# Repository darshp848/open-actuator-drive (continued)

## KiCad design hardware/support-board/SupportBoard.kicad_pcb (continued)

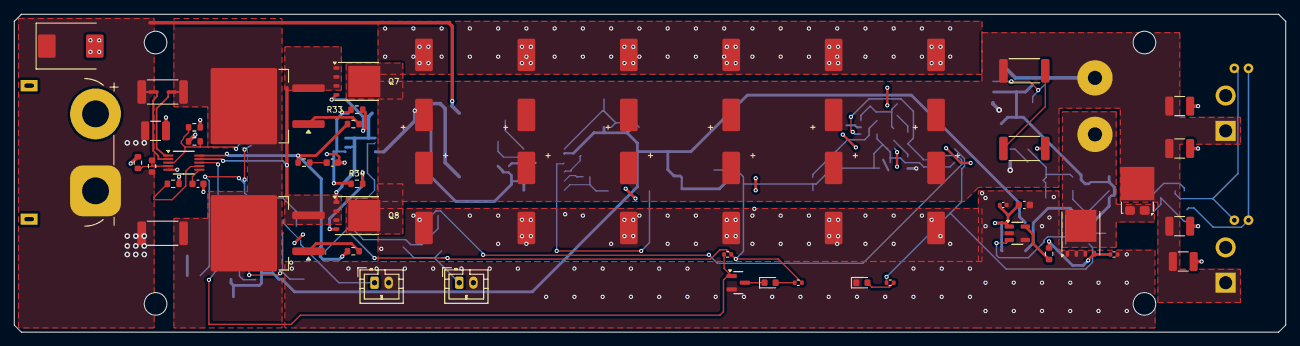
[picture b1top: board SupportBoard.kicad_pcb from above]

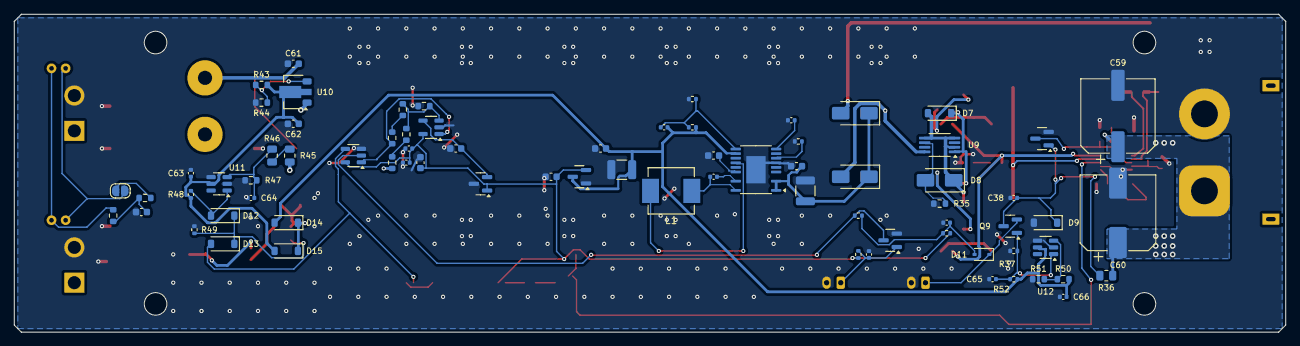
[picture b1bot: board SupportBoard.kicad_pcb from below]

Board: 2 copper layers, 180.0 x 45.0 mm, 139 parts (75 on the bottom side), 61 nets.

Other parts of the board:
H1, H2, H3, H4: MountingHole_3.2mm_M3

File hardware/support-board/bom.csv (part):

ref,value,mpn,footprint,block,note
J1,XT90PW-M battery,XT90PW-M,AMASS_XT90PW-M_1x02_P10.90mm_Horizontal,Input / hot-swap,"Battery input, male PCB XT90 (battery lead carries the female)"
D1,SMCJ58A,SMCJ58A-M3/57T,D_SMC,Input / hot-swap,"Input TVS, VBR 64.4-71.2 V, VC 93.6 V at 16 A (Vishay 88394); C59/C60 take the lead energy first"
C1,1uF 100V,GRM32ER72A105KA01L,C_1210_3225Metric,Input / hot-swap,VIN bypass at U1
C59,33uF 100V,875575961005,CP_Elec_10x12.6,Input / hot-swap,"Input energy absorber, Wurth hybrid polymer, 40 mOhm"
C60,47uF 100V,EEE-FN2A470UP,CP_Elec_10x10.5,Input / hot-swap,"Input damping, 0.7 ohm ESR damps the lead / ceramic LC ring"
RS1,1.8m 1% 3W,CSS2H-2512K-1L80FE,R_2512_6332Metric,Input / hot-swap,"Sense, 2 x 1.8 mOhm = 0.9 mOhm: I_LIM 53.4-69.0 A"
RS2,1.8m 1% 3W,CSS2H-2512K-1L80FE,R_2512_6332Metric,Input / hot-swap,
U1,LM5069MM-2/NOPB,LM5069MM-2/NOPB,VSSOP-10_3x3mm_P0.5mm,Input / hot-swap,
Q1,CSD19536KTT,CSD19536KTTT,TO-263-2,Input / hot-swap,
R3,10R,RC0603FR-0710RL,R_0603_1608Metric,Input / hot-swap,Per-FET gate resistor (parallel FETs)
Q2,CSD19536KTT,CSD19536KTTT,TO-263-2,Input / hot-swap,
R4,10R,RC0603FR-0710RL,R_0603_1608Metric,Input / hot-swap,Per-FET gate resistor (parallel FETs)
R5,71.5k 1%,RC0603FR-0771K5L,R_0603_1608Metric,Input / hot-swap,"UVLO: on 19.2 V, off 17.7 V (21 uA hysteresis)"
R6,10.7k 1%,RC0603FR-0710K7L,R_0603_1608Metric,Input / hot-swap,
R7,71.5k 1%,RC0603FR-0771K5L,R_0603_1608Metric,Input / hot-swap,"OVLO: off 59.1 V, on 57.6 V (above the 57.1 V chopper)"
R8,3.16k 1%,RC0603FR-073K16L,R_0603_1608Metric,Input / hot-swap,
R9,27.4k 1%,RC0603FR-0727K4L,R_0603_1608Metric,Input / hot-swap,Power limit 305 W at 54 V with 0.9 mOhm (VSNS 5.1 mV >= 5 mV floor)
C2,15nF,C0603C153K5RACTU,C_0603_1608Metric,Input / hot-swap,Fault timer 0.71 ms (0.42-1.35 ms); insertion delay 11 ms
R10,1k,RC0603FR-071KL,R_0603_1608Metric,Input / hot-swap,"dv/dt start: 16 uA / 47 nF = 340 V/s, ~1 A into 3 mF"
C3,47nF 100V,C0603C473K1RACTU,C_0603_1608Metric,Input / hot-swap,Gate-to-ground dv/dt capacitor sees about BUS + 12 V; DC-bias startup qualification remains open
Q4,BSS138,BSS138,SOT-23,Input / hot-swap,RUN_INH high (default) -> UVLO held low -> hot-swap off
R11,100k,RC0402FR-07100KL,R_0402_1005Metric,Input / hot-swap,
Q5,BSS138,BSS138,SOT-23,Input / hot-swap,
D5,green PGD,150060GS75000,LED_0603_1608Metric,Input / hot-swap,PGD released indication only; does not prove bus voltage or input validity
R12,1k,RC0402FR-071KL,R_0402_1005Metric,Input / hot-swap,
Q7,BSC040N10NS5ATMA1,BSC040N10NS5ATMA1,TDSON-8-1,Input / hot-swap,"Ideal-diode FET: source HS_S, drain BUS+ (2 x 4 mOhm in parallel)"
R33,10R,RC0603FR-0710RL,R_0603_1608Metric,Input / hot-swap,Per-FET gate resistor (parallel FETs)
Q8,BSC040N10NS5ATMA1,BSC040N10NS5ATMA1,TDSON-8-1,Input / hot-swap,"Ideal-diode FET: source HS_S, drain BUS+ (2 x 4 mOhm in parallel)"
R34,10R,RC0603FR-0710RL,R_0603_1608Metric,Input / hot-swap,Per-FET gate resistor (parallel FETs)
U9,LTC4359IMS8#PBF,LTC4359IMS8#PBF,MSOP-8_3x3mm_P0.65mm,Input / hot-swap,Ideal diode controller: blocks regeneration into the source
D7,BZT52C12,BZT52C12-7-F,D_SOD-123,Input / hot-swap,"12 V gate-source clamp (LTC4359 D4, required at 24 V and above)"
D8,SMAT70A,SMAT70A,D_SMA,Input / hot-swap,IN/SOURCE positive clamp to VSS (LTC4359 D1)
R35,1k,RC0603FR-071KL,R_0603_1608Metric,Input / hot-swap,VSS resistor (LTC4359 R1): keeps fast turn-off with the TVS
C20,130uF 80V,B40910A0137M000,TDK_B40910_10x16p5_DRAFT,Bank / chain outputs,
C21,130uF 80V,B40910A0137M000,TDK_B40910_10x16p5_DRAFT,Bank / chain outputs,
C22,130uF 80V,B40910A0137M000,TDK_B40910_10x16p5_DRAFT,Bank / chain outputs,
C23,130uF 80V,B40910A0137M000,TDK_B40910_10x16p5_DRAFT,Bank / chain outputs,
C24,130uF 80V,B40910A0137M000,TDK_B40910_10x16p5_DRAFT,Bank / chain outputs,
C25,130uF 80V,B40910A0137M000,TDK_B40910_10x16p5_DRAFT,Bank / chain outputs,
C26,130uF 80V,B40910A0137M000,TDK_B40910_10x16p5_DRAFT,Bank / chain outputs,
C27,130uF 80V,B40910A0137M000,TDK_B40910_10x16p5_DRAFT,Bank / chain outputs,
C28,130uF 80V,B40910A0137M000,TDK_B40910_10x16p5_DRAFT,Bank / chain outputs,
C29,130uF 80V,B40910A0137M000,TDK_B40910_10x16p5_DRAFT,Bank / chain outputs,
C30,130uF 80V,B40910A0137M000,TDK_B40910_10x16p5_DRAFT,Bank / chain outputs,
C31,130uF 80V,B40910A0137M000,TDK_B40910_10x16p5_DRAFT,Bank / chain outputs,
C32,1uF 100V,GRM32ER72A105KA01L,C_1210_3225Metric,Bank / chain outputs,HF bypass at the chain outputs
C33,1uF 100V,GRM32ER72A105KA01L,C_1210_3225Metric,Bank / chain outputs,HF bypass at the chain outputs
C34,1uF 100V,GRM32ER72A105KA01L,C_1210_3225Metric,Bank / chain outputs,HF bypass at the chain outputs
C35,1uF 100V,GRM32ER72A105KA01L,C_1210_3225Metric,Bank / chain outputs,HF bypass at the chain outputs
R13,10k 0.5W,RC2512FK-0710KL,R_2512_6332Metric,Bank / chain outputs,Bleeder: 3 mF from 54 V to 5 V in ~150 s
R14,10k 0.5W,RC2512FK-0710KL,R_2512_6332Metric,Bank / chain outputs,
J2,XT30PW(2+2)-M chain,XT30PW(2+2)-M.G.B,XT30PW22M,Bank / chain outputs,Same pinout as the actuator J1/J5
J3,XT30PW(2+2)-M chain,XT30PW(2+2)-M.G.B,XT30PW22M,Bank / chain outputs,Same pinout as the actuator J1/J5
JP1,CAN TERM,,SolderJumper-2_P1.3mm_Open_RoundedPad1.0x1.5mm,Bank / chain outputs,Close to terminate the chain at the support board
R15,60.4R,RC0603FR-0760R4L,R_0603_1608Metric,Bank / chain outputs,
R16,60.4R,RC0603FR-0760R4L,R_0603_1608Metric,Bank / chain outputs,
C36,4.7nF,GRM188R71H472KA01D,C_0603_1608Metric,Bank / chain outputs,
R20,150k 0.1%,TNPW0603150KBETA,R_0603_1608Metric,Brake chopper,Threshold 57.1 V on / 55.0 V off
R21,150k 0.1%,TNPW0603150KBETA,R_0603_1608Metric,Brake chopper,
R22,6.81k 0.1%,TNPW06036K81BETA,R_0603_1608Metric,Brake chopper,
R23,237k 0.1%,TNPW0603237KBETA,R_0603_1608Metric,Brake chopper,
R24,237k 0.1%,TNPW0603237KBETA,R_0603_1608Metric,Brake chopper,
U3,TLV3201AIDBVR,TLV3201AIDBVR,SOT-23-5,Brake chopper,
U4,REF3312AIDBZR,REF3312AIDBZR,SOT-23,Brake chopper,
C40,0.1uF,GCM155R71E104KE02D,C_0402_1005Metric,Brake chopper,
C41,1uF,C1608X7R1E105K080AE,C_0603_1608Metric,Brake chopper,
C42,1uF,C1608X7R1E105K080AE,C_0603_1608Metric,Brake chopper,
U5,SN74LVC1G32DBVR,SN74LVC1G32DBVR,SOT-23-5,Brake chopper,Chopper on = overvoltage OR discharge request
C43,0.1uF,GCM155R71E104KE02D,C_0402_1005Metric,Brake chopper,
U6,UCC27517DBVR,UCC27517DBVT,SOT-23-5,Brake chopper,IN+ = primary CH_CMD OR backup CHB_OV; VDD = +12V OR V_CHB (aux-loss fix 2026-10-25)
C44,0.1uF 25V,GCM155R71E104KE02D,C_0402_1005Metric,Brake chopper,
C45,1uF 25V,C1608X7R1E105K080AE,C_0603_1608Metric,Brake chopper,
D13,1N5819HW,1N5819HW-7-F,D_SOD-123,Brake chopper,Primary command into the driver OR (3.2 V - 0.3 V > VIN_H 2.4 V)
R49,100k,RC0402FR-07100KL,R_0402_1005Metric,Brake chopper,Driver input pull-down
D14,1N5819HW,1N5819HW-7-F,D_SOD-123,Brake chopper,Driver supply from the aux 12 V
R25,4.7R,RC0603FR-074R7L,R_0603_1608Metric,Brake chopper,
R26,10k,RC0402FR-0710KL,R_0402_1005Metric,Brake chopper,
Q3,BSC040N10NS5ATMA1,BSC040N10NS5ATMA1,TDSON-8-1,Brake chopper,Chopper switch: 21.6 A into 2.5 ohm at 54 V
D2,V10P10-M3/86A,V10P10-M3/86A,TO-277A,Brake chopper,Freewheel across the resistor harness
J4,BRAKE RESISTOR,,PowerWire_P8,Brake chopper,"Wire pads to BrakeResistor J1 (1 = BRK+, 2 = switched end)"
D6,red BRAKE,150060RS75000,LED_0603_1608Metric,Brake chopper,
R27,1k,RC0402FR-071KL,R_0402_1005Metric,Brake chopper,
U10,LR8N8-G,LR8N8-G,SOT-89-3,Backup OV brake,Bus-powered 10 V for the backup channel (9.5-10.7 V); needs BUS+ >= 22.7 V
C61,0.1uF 100V,GCJ188R72A104KA01D,C_0603_1608Metric,Backup OV brake,
R43,2.4k 1%,RC0603FR-072K4L,R_0603_1608Metric,Backup OV brake,LR8 R1: also its 0.5 mA minimum load
R44,17.4k 1%,RC0603FR-0717K4L,R_0603_1608Metric,Backup OV brake,LR8 R2: 1.20 V x 8.25 + 10 uA x 17.4k = 10.07 V
C62,1uF 25V,C1608X7R1E105K080AE,C_0603_1608Metric,Backup OV brake,LR8 output (>= 1 uF)
D15,1N5819HW,1N5819HW-7-F,D_SOD-123,Backup OV brake,Driver supply from the bus when the aux is gone
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
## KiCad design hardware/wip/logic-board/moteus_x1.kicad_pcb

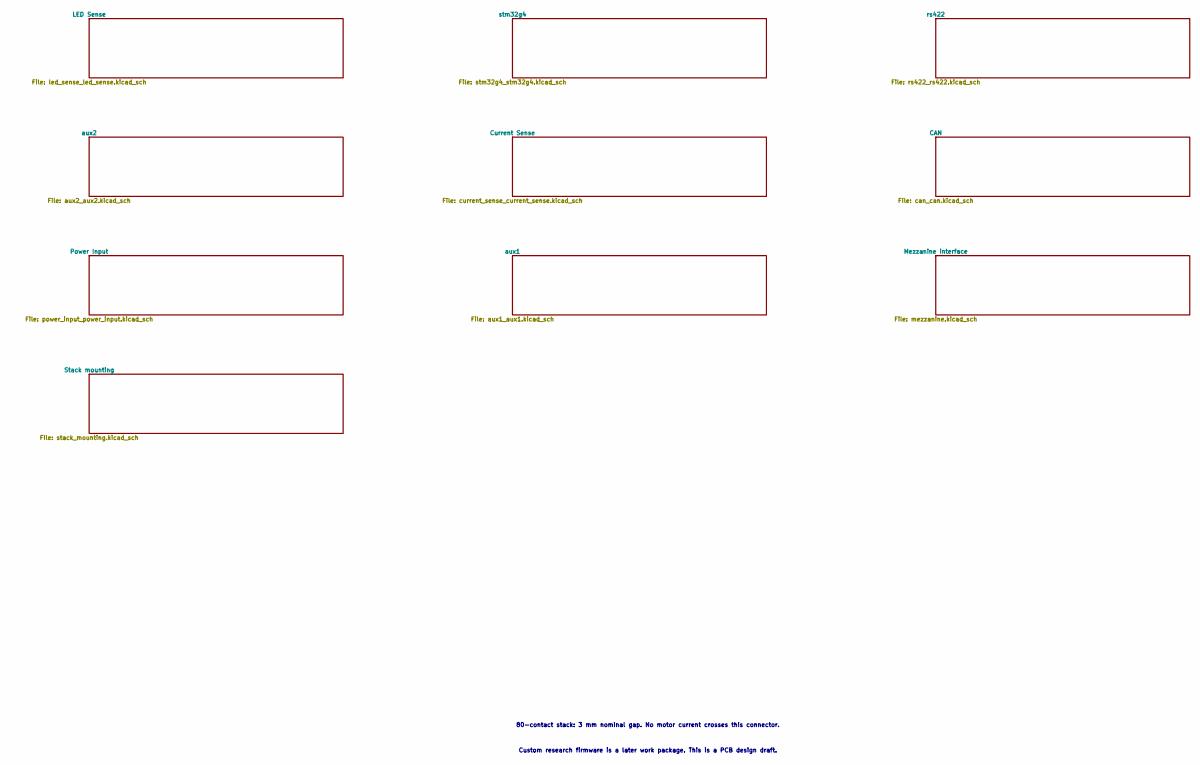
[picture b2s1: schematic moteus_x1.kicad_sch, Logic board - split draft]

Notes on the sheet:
Custom research firmware is a later work package. This is a PCB design draft.
80-contact stack: 3 mm nominal gap. No motor current crosses this connector.

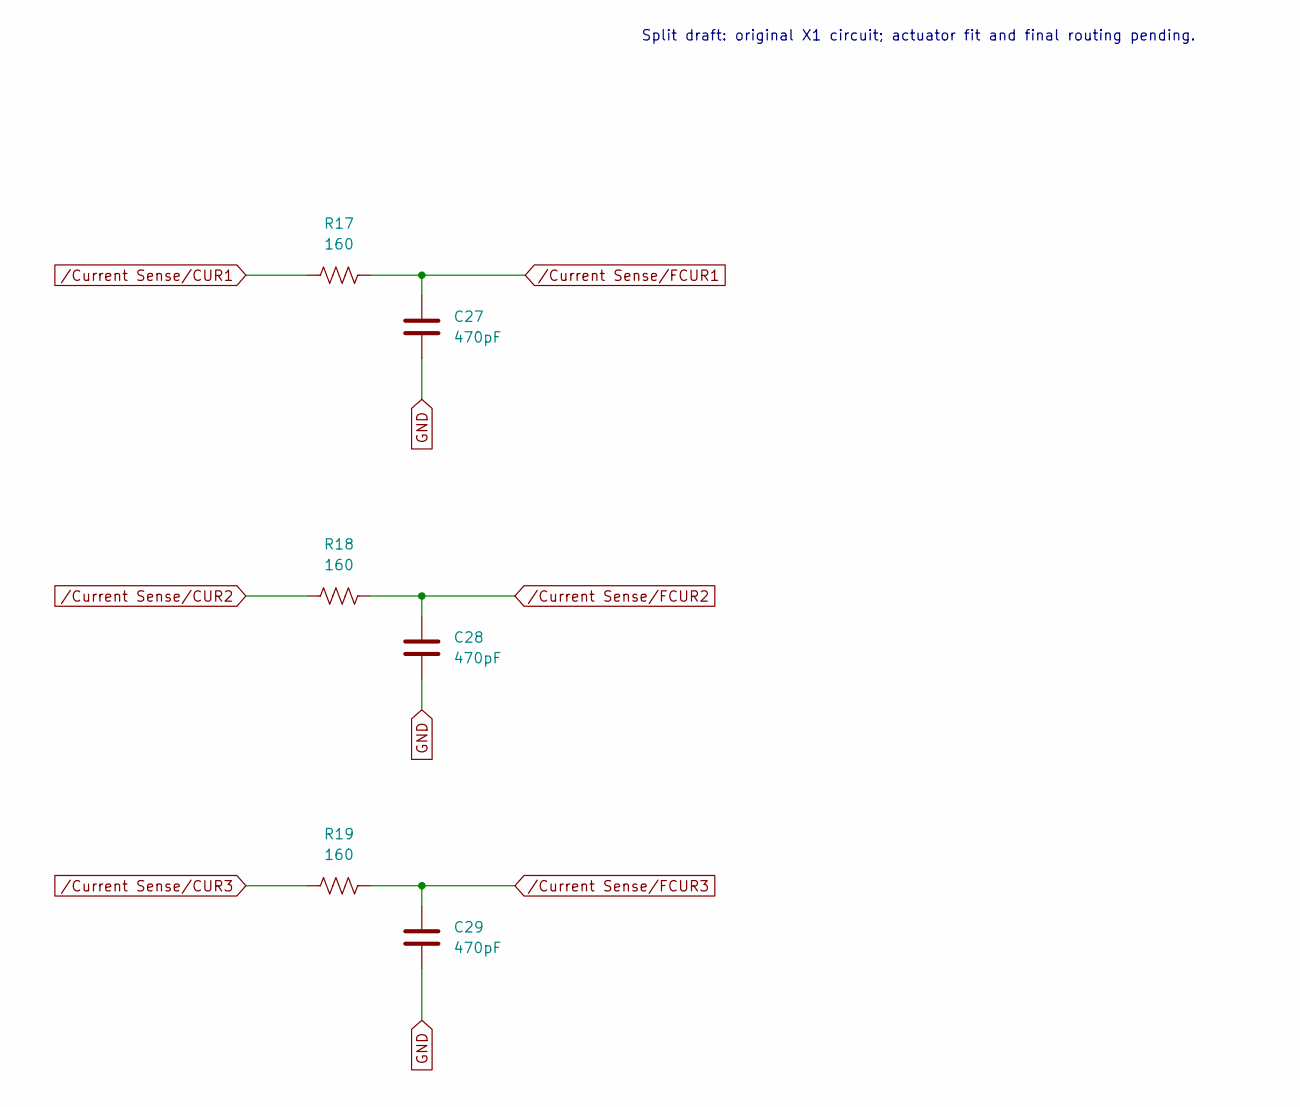
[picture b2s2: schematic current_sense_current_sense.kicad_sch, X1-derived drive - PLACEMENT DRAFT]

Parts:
C27, C28, C29: 470pF; C_0402_1005Metric; MPN GCM1555C1H471JA16D
R17, R18, R19: 160; R_0402_1005Metric; MPN RC0402FR-07160RL

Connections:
GND: C27.2, C28.2, C29.2; also elsewhere on the board
/Current Sense/CUR1: R17.1; also elsewhere on the board
/Current Sense/CUR2: R18.1; also elsewhere on the board
/Current Sense/CUR3: R19.1; also elsewhere on the board
/Current Sense/FCUR1: C27.1, R17.2; also elsewhere on the board
/Current Sense/FCUR2: C28.1, R18.2; also elsewhere on the board
/Current Sense/FCUR3: C29.1, R19.2; also elsewhere on the board

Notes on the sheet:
Split draft: original X1 circuit; actuator fit and final routing pending.

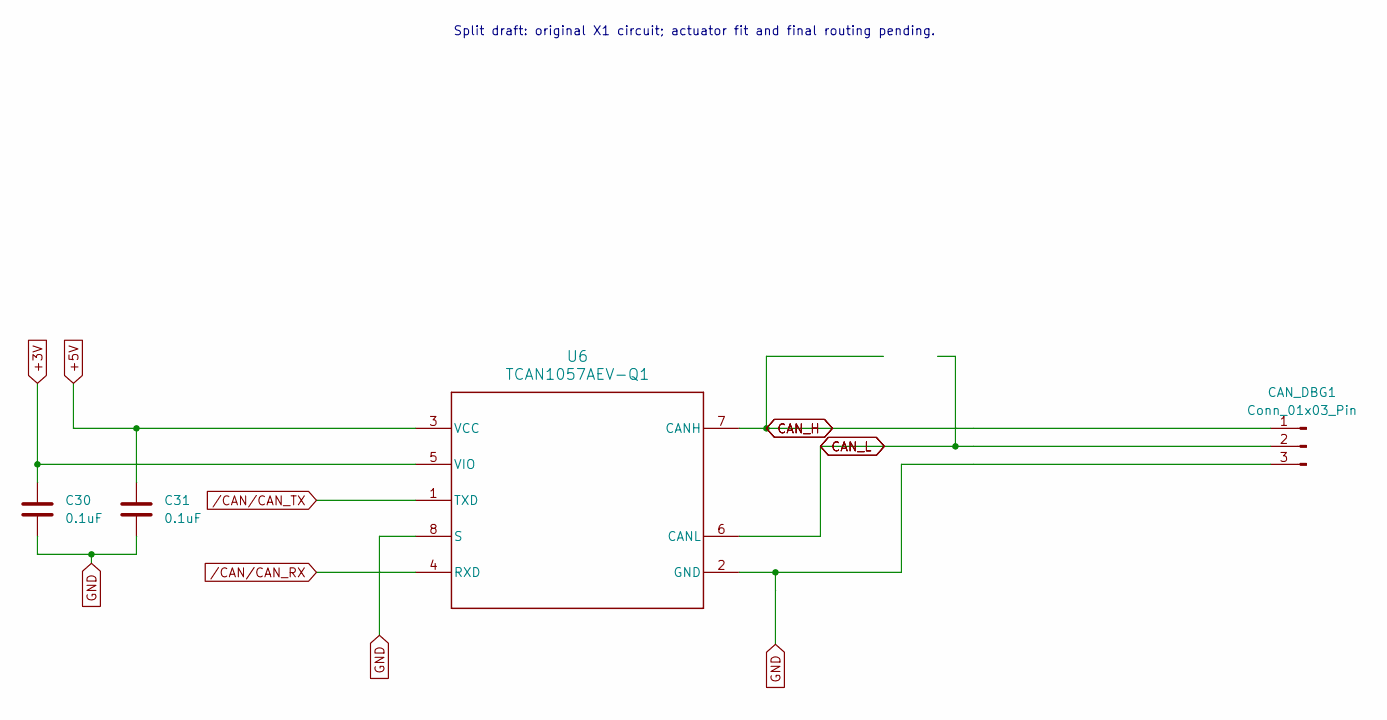
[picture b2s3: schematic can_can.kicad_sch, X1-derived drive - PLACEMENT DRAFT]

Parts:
C30, C31: 0.1uF; C_0402_1005Metric; MPN MF-CAP-0402-0.1uF
CAN_DBG1: Conn_01x03_Pin; PinHeader_1x03_P2.00mm_Vertical
U6: TCAN1057AEV-Q1; SOIC-8_3.9x4.9mm_P1.27mm; MPN TCAN1057AEVDRQ1

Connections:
+3V: C30.1, U6.5 (VIO); also elsewhere on the board
+5V: C31.1, U6.3 (VCC); also elsewhere on the board
CAN_H: CAN_DBG1.1, U6.7 (CANH); also elsewhere on the board
CAN_L: CAN_DBG1.2, U6.6 (CANL); also elsewhere on the board
GND: C30.2, C31.2, CAN_DBG1.3, U6.2 (GND), U6.8 (S); also elsewhere on the board
/CAN/CAN_RX: U6.4 (RXD); also elsewhere on the board
/CAN/CAN_TX: U6.1 (TXD); also elsewhere on the board

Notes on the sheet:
Split draft: original X1 circuit; actuator fit and final routing pending.

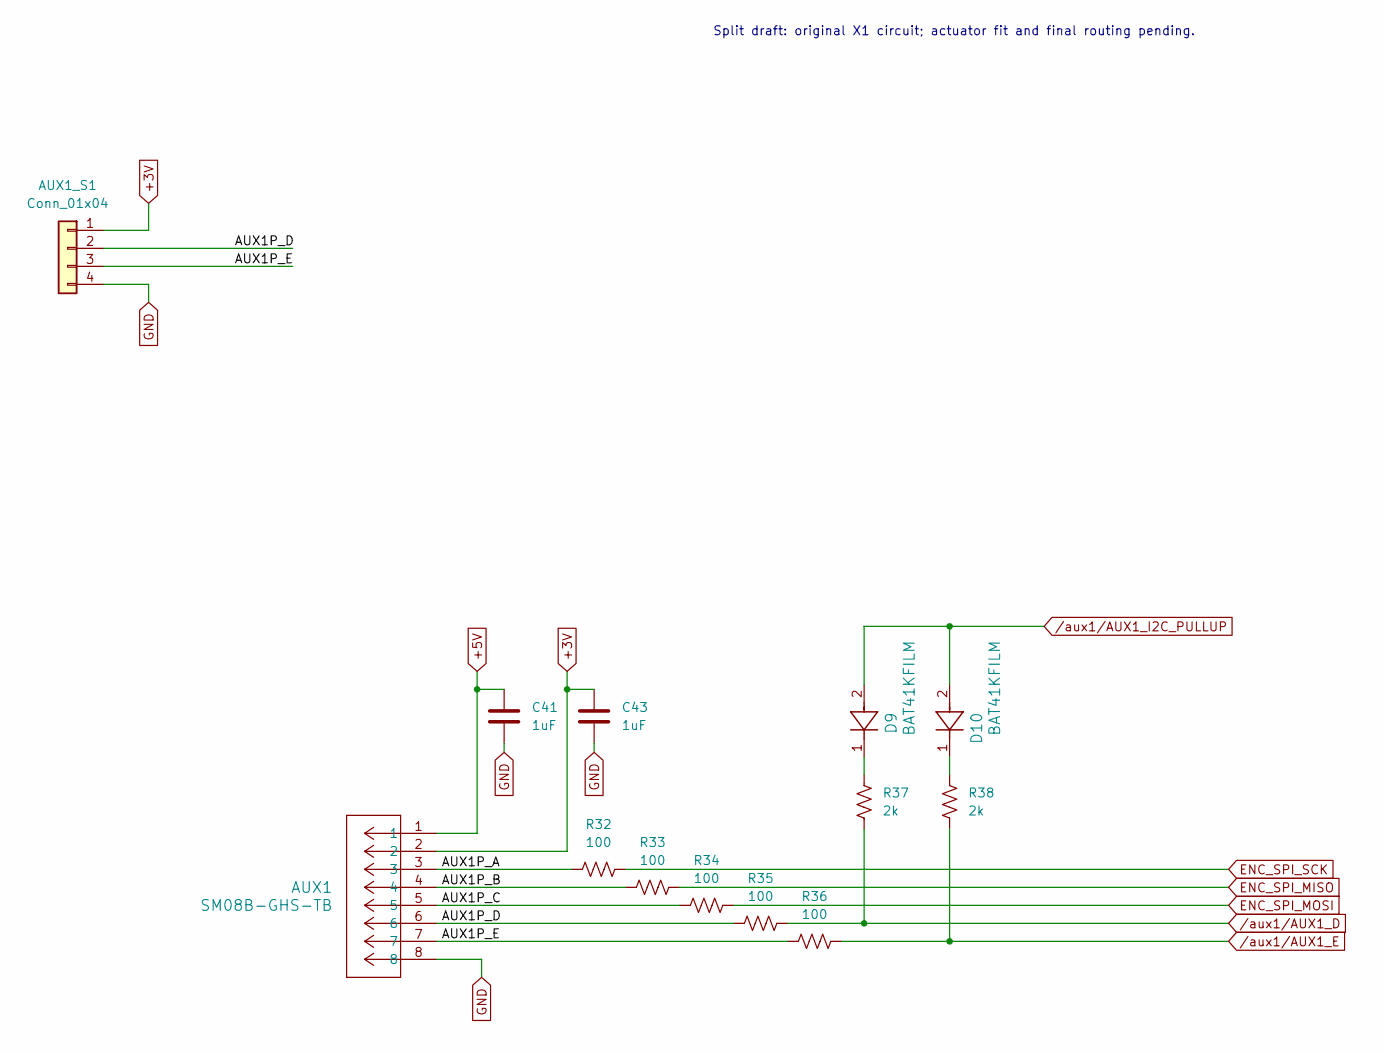
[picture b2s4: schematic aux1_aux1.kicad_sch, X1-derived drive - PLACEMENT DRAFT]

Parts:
AUX1: SM08B-GHS-TB; CONN_SM08B-GHS-TB_JST; MPN SM08B-GHS-TB(LF)(SN)
AUX1_S1: Conn_01x04; PinHeader_1x04_P1.27mm_Vertical
C41, C43: 1uF; C_0402_1005Metric; MPN MF-CAP-0402-1uF
D9, D10: BAT41KFILM; SOD-523_STM; MPN BAT41KFILM
R32, R33, R34, R35, R36: 100; R_0402_1005Metric; MPN MF-RES-0402-100
R37, R38: 2k; R_0402_1005Metric; MPN MF-RES-0402-2K

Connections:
+3V: AUX1.2, AUX1_S1.1, C43.1; also elsewhere on the board
+5V: AUX1.1, C41.1; also elsewhere on the board
/aux1/AUX1P_A: AUX1.3, R32.1
/aux1/AUX1P_B: AUX1.4, R33.1
/aux1/AUX1P_C: AUX1.5, R34.1
/aux1/AUX1P_D: AUX1.6, AUX1_S1.2, R35.1
/aux1/AUX1P_E: AUX1.7, AUX1_S1.3, R36.1
ENC_SPI_MISO: R33.2; also elsewhere on the board
ENC_SPI_MOSI: R34.2; also elsewhere on the board
ENC_SPI_SCK: R32.2; also elsewhere on the board
GND: AUX1.8, AUX1_S1.4, C41.2, C43.2; also elsewhere on the board
unnamed: D9.1, R37.1
unnamed: D10.1, R38.1
/aux1/AUX1_D: R35.2, R37.2; also elsewhere on the board
/aux1/AUX1_E: R36.2, R38.2; also elsewhere on the board
/aux1/AUX1_I2C_PULLUP: D9.2, D10.2; also elsewhere on the board

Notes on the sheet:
Split draft: original X1 circuit; actuator fit and final routing pending.

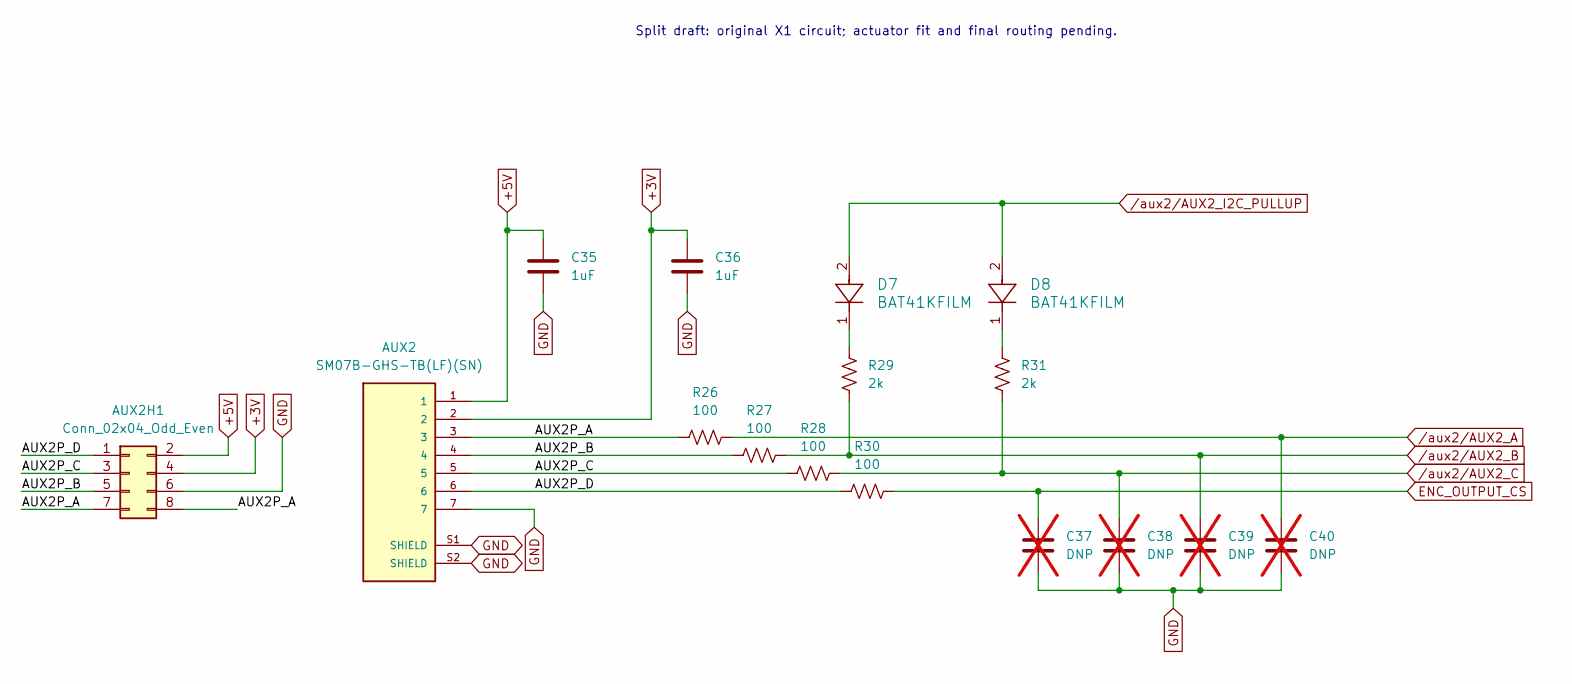
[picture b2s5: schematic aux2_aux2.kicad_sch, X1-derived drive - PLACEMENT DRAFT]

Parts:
AUX2: SM07B-GHS-TB(LF)(SN); JST_SM07B-GHS-TB(LF)(SN); MPN SM07B-GHS-TB(LF)(SN)
AUX2H1: Conn_02x04_Odd_Even; PinHeader_2x04_P1.27mm_Vertical
C35, C36: 1uF; C_0402_1005Metric; MPN MF-CAP-0402-1uF
C37, C38, C39, C40: DNP; C_0402_1005Metric; not fitted
D7, D8: BAT41KFILM; SOD-523_STM; MPN BAT41KFILM
R26, R27, R28, R30: 100; R_0402_1005Metric; MPN MF-RES-0402-100
R29, R31: 2k; R_0402_1005Metric; MPN MF-RES-0402-2K

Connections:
+3V: AUX2.2, AUX2H1.4, C36.1; also elsewhere on the board
+5V: AUX2.1, AUX2H1.2, C35.1; also elsewhere on the board
/aux2/AUX2P_A: AUX2.3, AUX2H1.7, AUX2H1.8, R26.1
/aux2/AUX2P_B: AUX2.4, AUX2H1.5, R27.1
/aux2/AUX2P_C: AUX2.5, AUX2H1.3, R28.1
/aux2/AUX2P_D: AUX2.6, AUX2H1.1, R30.1
ENC_OUTPUT_CS: C37.1, R30.2; also elsewhere on the board
GND: AUX2.7, AUX2.S1 (SHIELD), AUX2.S2 (SHIELD), AUX2H1.6, C35.2, C36.2, C37.2, C38.2, C39.2, C40.2; also elsewhere on the board
unnamed: D7.1, R29.1
unnamed: D8.1, R31.1
/aux2/AUX2_A: C40.1, R26.2; also elsewhere on the board
/aux2/AUX2_B: C39.1, R27.2, R29.2; also elsewhere on the board
/aux2/AUX2_C: C38.1, R28.2, R31.2; also elsewhere on the board
/aux2/AUX2_I2C_PULLUP: D7.2, D8.2; also elsewhere on the board

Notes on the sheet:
Split draft: original X1 circuit; actuator fit and final routing pending.

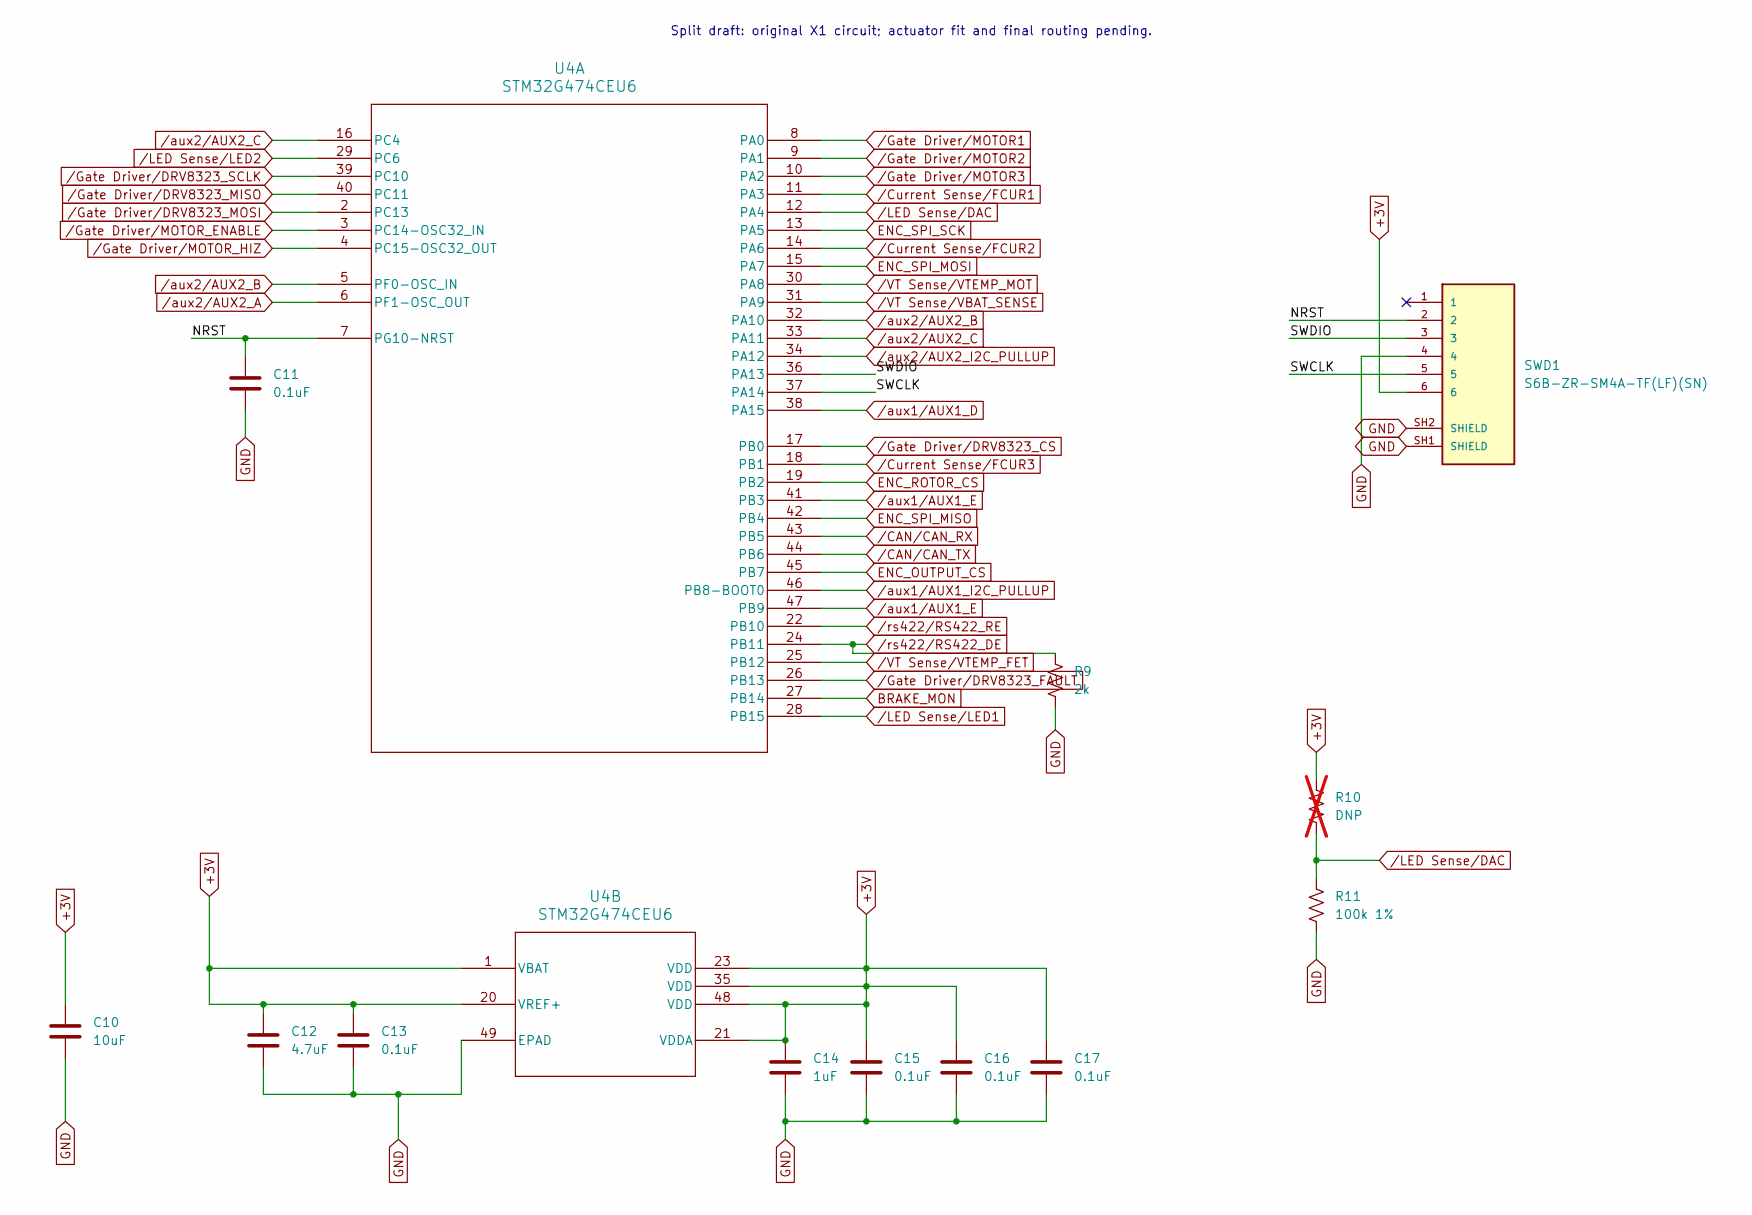
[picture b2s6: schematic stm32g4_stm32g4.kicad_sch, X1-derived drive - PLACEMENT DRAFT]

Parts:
C10: 10uF; C_1206_3216Metric; MPN MF-CAP-1206-10uF
C11, C13, C15, C16, C17: 0.1uF; C_0402_1005Metric; MPN MF-CAP-0402-0.1uF
C12: 4.7uF; C_0603_1608Metric; MPN CL10A475KP8NNNC
C14: 1uF; C_0402_1005Metric; MPN MF-CAP-0402-1uF
R9: 2k; R_0402_1005Metric; MPN MF-RES-0402-2K
R10: DNP; R_0402_1005Metric; not fitted
R11: 100k 1%; R_0402_1005Metric; MPN RC0402FR-07100KL
SWD1: S6B-ZR-SM4A-TF(LF)(SN); JST_S6B-ZR-SM4A-TF(LF)(SN); MPN S6B-ZR-SM4A-TF(LF)(SN)
U4: STM32G474CEU6; UFQFPN-48_7X7X0P55MM; MPN STM32G474CEU6

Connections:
+3V: C10.1, C12.1, C13.1, C14.1, C15.1, C16.1, C17.1, R10.1, SWD1.6, U4.1 (VBAT), U4.20 (VREF+), U4.21 (VDDA), U4.23 (VDD), U4.35 (VDD), U4.48 (VDD); also elsewhere on the board
/stm32g4/NRST: C11.1, SWD1.2, U4.7 (PG10-NRST)
/stm32g4/SWCLK: SWD1.5, U4.37 (PA14)
/stm32g4/SWDIO: SWD1.3, U4.36 (PA13)
BRAKE_MON: U4.27 (PB14); also elsewhere on the board
ENC_OUTPUT_CS: U4.45 (PB7); also elsewhere on the board
ENC_ROTOR_CS: U4.19 (PB2); also elsewhere on the board
ENC_SPI_MISO: U4.42 (PB4); also elsewhere on the board
ENC_SPI_MOSI: U4.15 (PA7); also elsewhere on the board
ENC_SPI_SCK: U4.13 (PA5); also elsewhere on the board
GND: C10.2, C11.2, C12.2, C13.2, C14.2, C15.2, C16.2, C17.2, R9.2, R11.2, SWD1.4, SWD1.SH1 (SHIELD), SWD1.SH2 (SHIELD), U4.49 (EPAD); also elsewhere on the board
/CAN/CAN_RX: U4.43 (PB5); also elsewhere on the board
/CAN/CAN_TX: U4.44 (PB6); also elsewhere on the board
/Current Sense/FCUR1: U4.11 (PA3); also elsewhere on the board
/Current Sense/FCUR2: U4.14 (PA6); also elsewhere on the board
/Current Sense/FCUR3: U4.18 (PB1); also elsewhere on the board
/Gate Driver/DRV8323_CS: U4.17 (PB0); also elsewhere on the board
/Gate Driver/DRV8323_FAULT: U4.26 (PB13); also elsewhere on the board
/Gate Driver/DRV8323_MISO: U4.40 (PC11); also elsewhere on the board
/Gate Driver/DRV8323_MOSI: U4.2 (PC13); also elsewhere on the board
/Gate Driver/DRV8323_SCLK: U4.39 (PC10); also elsewhere on the board
/Gate Driver/MOTOR1: U4.8 (PA0); also elsewhere on the board
/Gate Driver/MOTOR2: U4.9 (PA1); also elsewhere on the board
/Gate Driver/MOTOR3: U4.10 (PA2); also elsewhere on the board
/Gate Driver/MOTOR_ENABLE: U4.3 (PC14-OSC32_IN); also elsewhere on the board
/Gate Driver/MOTOR_HIZ: U4.4 (PC15-OSC32_OUT); also elsewhere on the board
/LED Sense/DAC: R10.2, R11.1, U4.12 (PA4); also elsewhere on the board
/LED Sense/LED1: U4.28 (PB15); also elsewhere on the board
/LED Sense/LED2: U4.29 (PC6); also elsewhere on the board
/VT Sense/VBAT_SENSE: U4.31 (PA9); also elsewhere on the board
/VT Sense/VTEMP_FET: U4.25 (PB12); also elsewhere on the board
/VT Sense/VTEMP_MOT: U4.30 (PA8); also elsewhere on the board
/aux1/AUX1_D: U4.38 (PA15); also elsewhere on the board
/aux1/AUX1_E: U4.41 (PB3), U4.47 (PB9); also elsewhere on the board
/aux1/AUX1_I2C_PULLUP: U4.46 (PB8-BOOT0); also elsewhere on the board
/aux2/AUX2_A: U4.6 (PF1-OSC_OUT); also elsewhere on the board
/aux2/AUX2_B: U4.5 (PF0-OSC_IN), U4.32 (PA10); also elsewhere on the board
/aux2/AUX2_C: U4.16 (PC4), U4.33 (PA11); also elsewhere on the board
/aux2/AUX2_I2C_PULLUP: U4.34 (PA12); also elsewhere on the board
/rs422/RS422_DE: R9.1, U4.24 (PB11); also elsewhere on the board
/rs422/RS422_RE: U4.22 (PB10); also elsewhere on the board

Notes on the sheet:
Split draft: original X1 circuit; actuator fit and final routing pending.

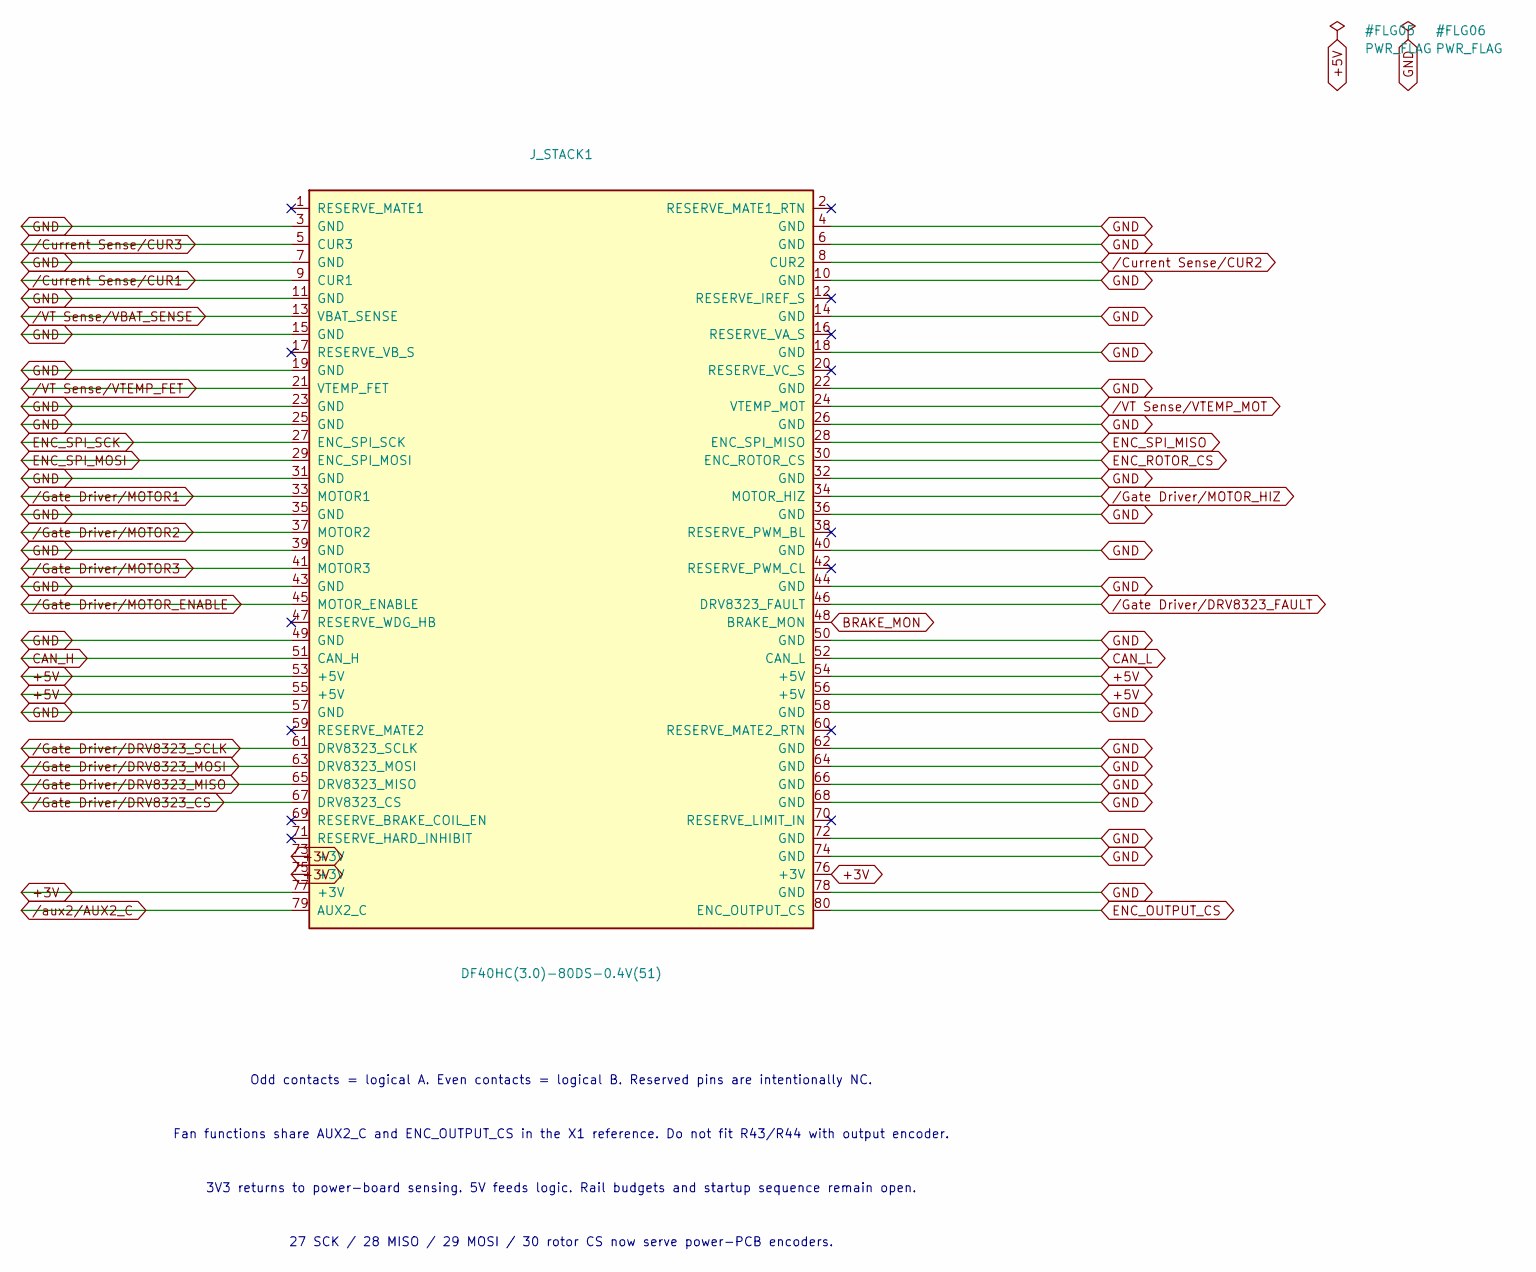
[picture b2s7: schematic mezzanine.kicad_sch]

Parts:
J_STACK1: DF40HC(3.0)-80DS-0.4V(51); Hirose_DF40HC(3.0)-80DS-0.4V_2x40_P0.4mm; MPN DF40HC(3.0)-80DS-0.4V(51)

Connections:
+3V: J_STACK1.73 (+3V), J_STACK1.75 (+3V), J_STACK1.76 (+3V), J_STACK1.77 (+3V); also elsewhere on the board
+5V: J_STACK1.53 (+5V), J_STACK1.54 (+5V), J_STACK1.55 (+5V), J_STACK1.56 (+5V); also elsewhere on the board
BRAKE_MON: J_STACK1.48 (BRAKE_MON); also elsewhere on the board
CAN_H: J_STACK1.51 (CAN_H); also elsewhere on the board
CAN_L: J_STACK1.52 (CAN_L); also elsewhere on the board
ENC_OUTPUT_CS: J_STACK1.80 (ENC_OUTPUT_CS); also elsewhere on the board
ENC_ROTOR_CS: J_STACK1.30 (ENC_ROTOR_CS); also elsewhere on the board
ENC_SPI_MISO: J_STACK1.28 (ENC_SPI_MISO); also elsewhere on the board
ENC_SPI_MOSI: J_STACK1.29 (ENC_SPI_MOSI); also elsewhere on the board
ENC_SPI_SCK: J_STACK1.27 (ENC_SPI_SCK); also elsewhere on the board
GND: J_STACK1.3 (GND), J_STACK1.4 (GND), J_STACK1.6 (GND), J_STACK1.7 (GND), J_STACK1.10 (GND), J_STACK1.11 (GND), J_STACK1.14 (GND), J_STACK1.15 (GND), J_STACK1.18 (GND), J_STACK1.19 (GND), J_STACK1.22 (GND), J_STACK1.23 (GND), J_STACK1.25 (GND), J_STACK1.26 (GND), J_STACK1.31 (GND), J_STACK1.32 (GND), J_STACK1.35 (GND), J_STACK1.36 (GND), J_STACK1.39 (GND), J_STACK1.40 (GND), J_STACK1.43 (GND), J_STACK1.44 (GND), J_STACK1.49 (GND), J_STACK1.50 (GND), J_STACK1.57 (GND), J_STACK1.58 (GND), J_STACK1.62 (GND), J_STACK1.64 (GND), J_STACK1.66 (GND), J_STACK1.68 (GND), J_STACK1.72 (GND), J_STACK1.74 (GND), J_STACK1.78 (GND); also elsewhere on the board
/Current Sense/CUR1: J_STACK1.9 (CUR1); also elsewhere on the board
/Current Sense/CUR2: J_STACK1.8 (CUR2); also elsewhere on the board
/Current Sense/CUR3: J_STACK1.5 (CUR3); also elsewhere on the board
/Gate Driver/DRV8323_CS: J_STACK1.67 (DRV8323_CS); also elsewhere on the board
/Gate Driver/DRV8323_FAULT: J_STACK1.46 (DRV8323_FAULT); also elsewhere on the board
/Gate Driver/DRV8323_MISO: J_STACK1.65 (DRV8323_MISO); also elsewhere on the board
/Gate Driver/DRV8323_MOSI: J_STACK1.63 (DRV8323_MOSI); also elsewhere on the board
/Gate Driver/DRV8323_SCLK: J_STACK1.61 (DRV8323_SCLK); also elsewhere on the board
/Gate Driver/MOTOR1: J_STACK1.33 (MOTOR1); also elsewhere on the board
/Gate Driver/MOTOR2: J_STACK1.37 (MOTOR2); also elsewhere on the board
/Gate Driver/MOTOR3: J_STACK1.41 (MOTOR3); also elsewhere on the board
/Gate Driver/MOTOR_ENABLE: J_STACK1.45 (MOTOR_ENABLE); also elsewhere on the board
/Gate Driver/MOTOR_HIZ: J_STACK1.34 (MOTOR_HIZ); also elsewhere on the board
/VT Sense/VBAT_SENSE: J_STACK1.13 (VBAT_SENSE); also elsewhere on the board
/VT Sense/VTEMP_FET: J_STACK1.21 (VTEMP_FET); also elsewhere on the board
/VT Sense/VTEMP_MOT: J_STACK1.24 (VTEMP_MOT); also elsewhere on the board
/aux2/AUX2_C: J_STACK1.79 (AUX2_C); also elsewhere on the board

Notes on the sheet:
Fan functions share AUX2_C and ENC_OUTPUT_CS in the X1 reference. Do not fit R43/R44 with output encoder.
Odd contacts = logical A. Even contacts = logical B. Reserved pins are intentionally NC.
27 SCK / 28 MISO / 29 MOSI / 30 rotor CS now serve power-PCB encoders.
3V3 returns to power-board sensing. 5V feeds logic. Rail budgets and startup sequence remain open.
